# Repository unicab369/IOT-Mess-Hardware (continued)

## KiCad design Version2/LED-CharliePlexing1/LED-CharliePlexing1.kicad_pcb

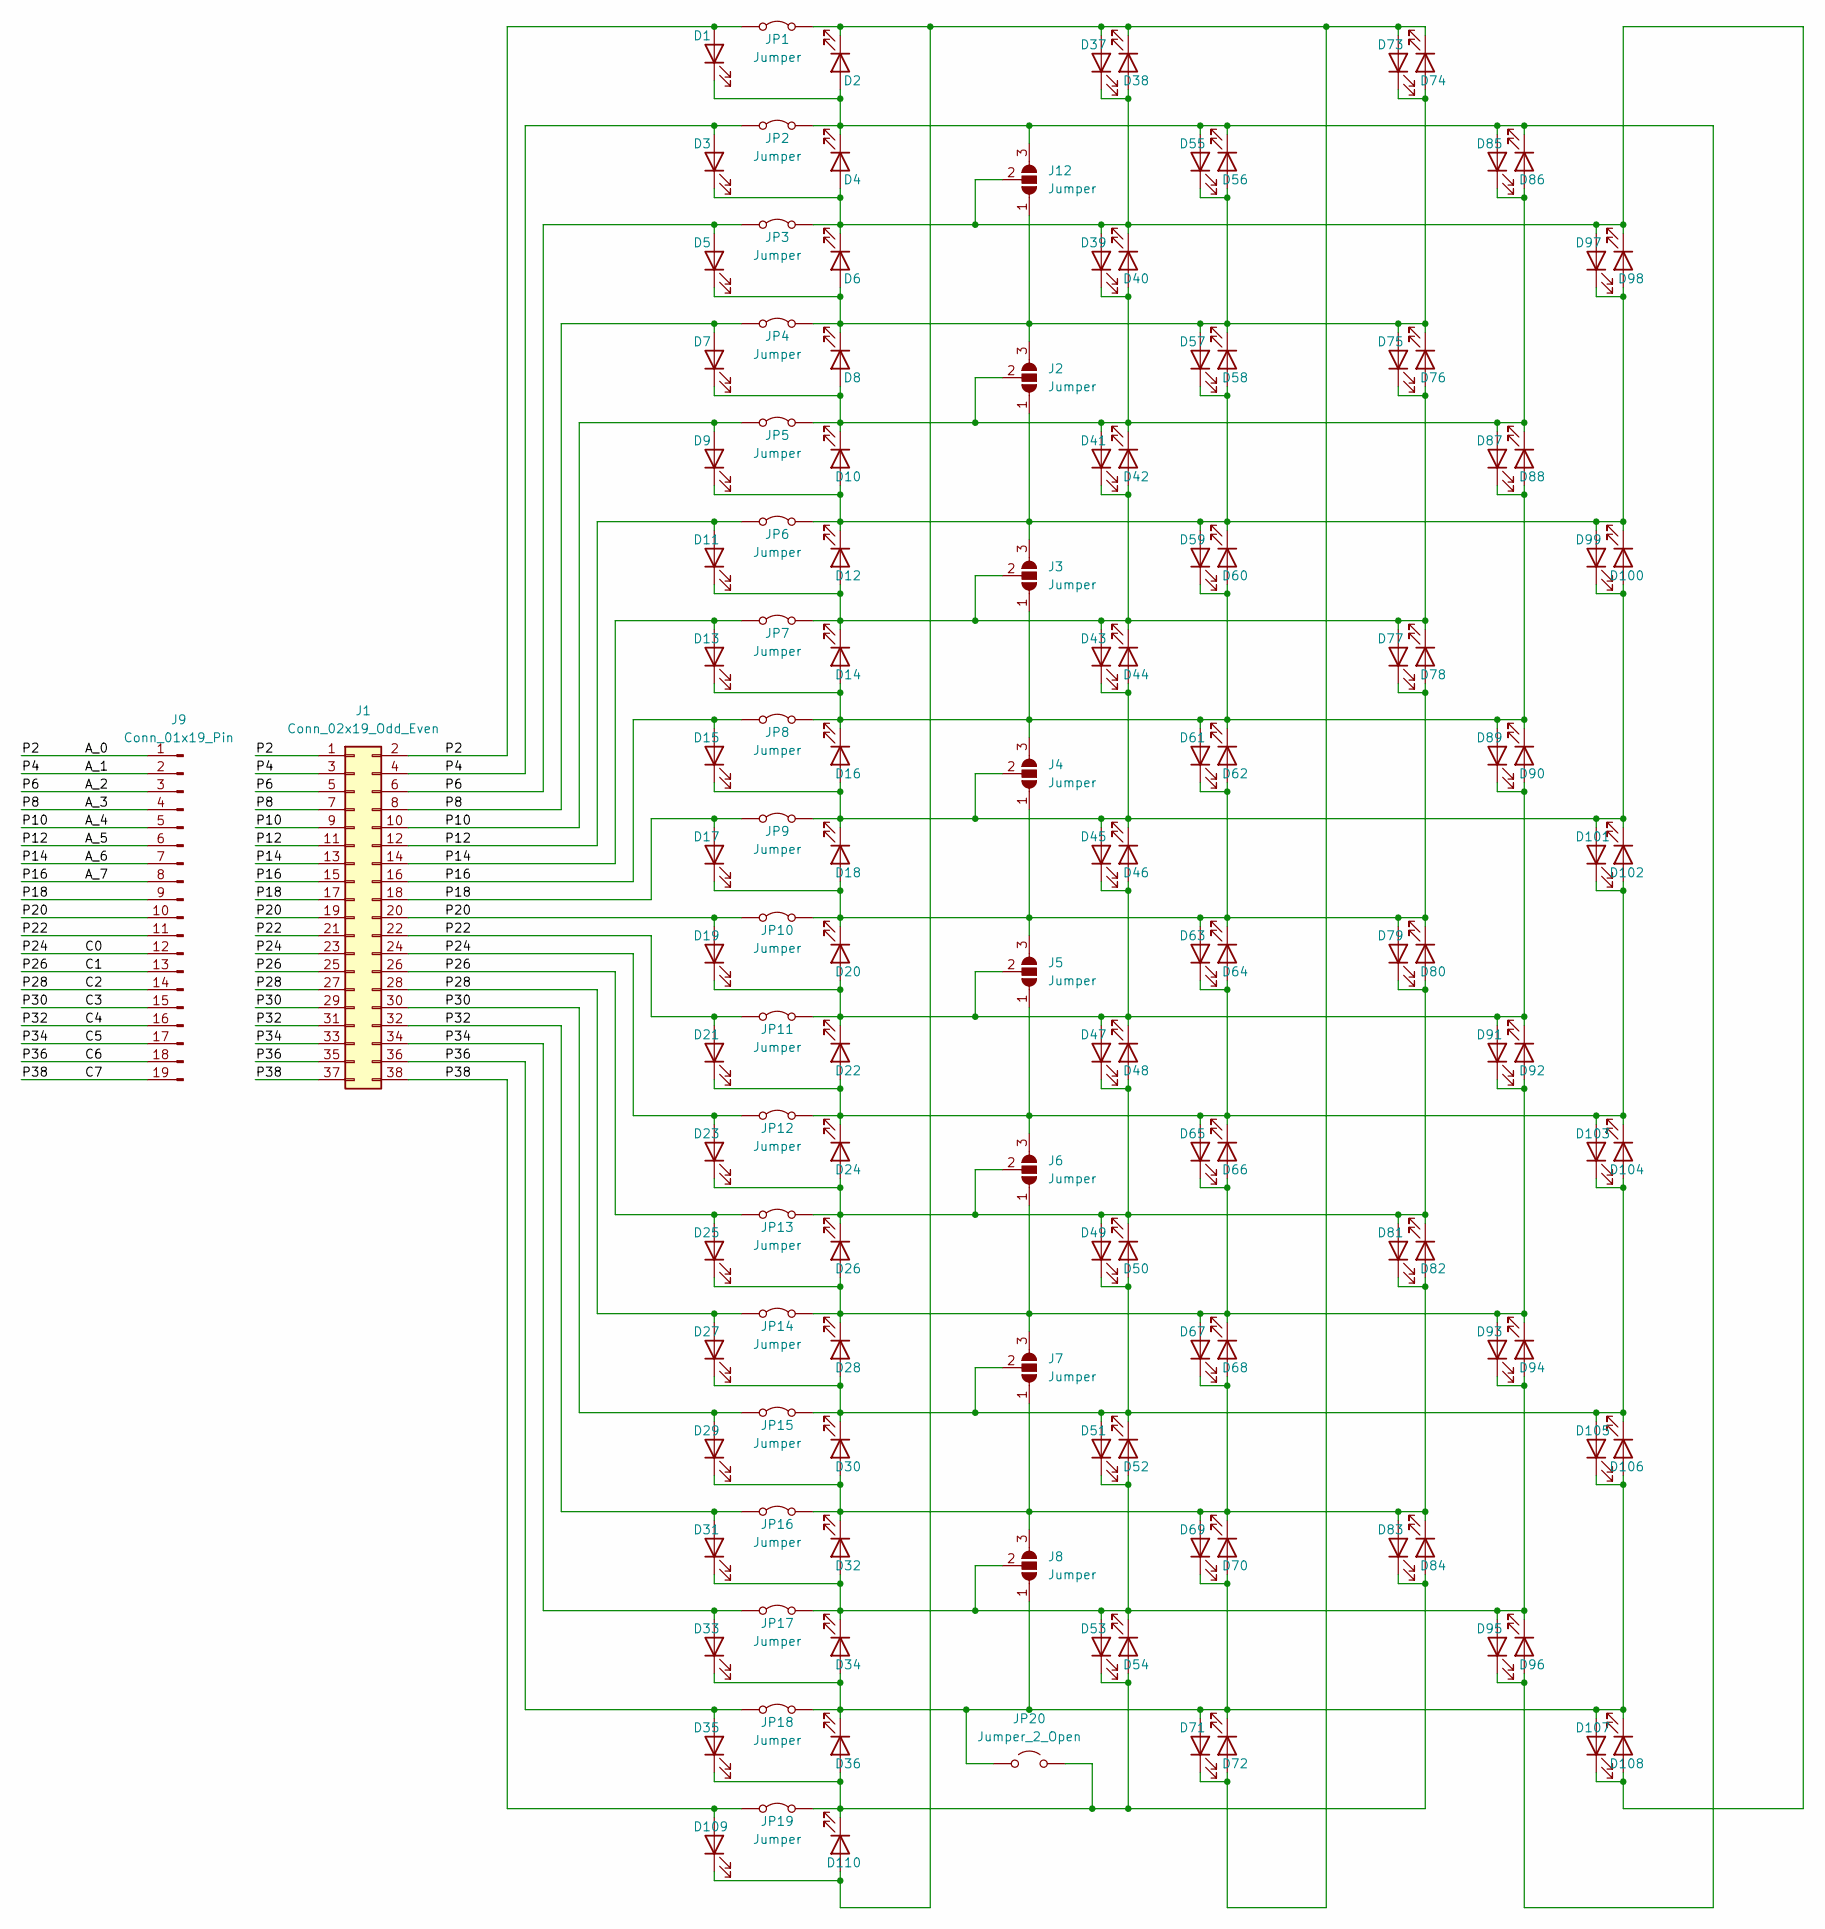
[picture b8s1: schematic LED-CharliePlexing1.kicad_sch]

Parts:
D1, D2, D3, D4, D5, D6, D7, D8, D9, D10, D11, D12, D13, D14, D15, D16, D17, D18, D19, D20, D21, D22, D23, D24, D25, D26, D27, D28, D29, D30, D31, D32, D33, D34, D35, D36, D37, D38, D39, D40, D41, D42, D43, D44, D45, D46, D47, D48, D49, D50, D51, D52, D53, D54, D55, D56, D57, D58, D59, D60, D61, D62, D63, D64, D65, D66, D67, D68, D69, D70, D71, D72, D73, D74, D75, D76, D77, D78, D79, D80, D81, D82, D83, D84, D85, D86, D87, D88, D89, D90, D91, D92, D93, D94, D95, D96, D97, D98, D99, D100, D101, D102, D103, D104, D105, D106, D107, D108, D109, D110: LED; LED_0603_1608Metric_Pad1.05x0.95mm_HandSolder
J1: Conn_02x19_Odd_Even; PinHeader_2x19_P2.54mm_Vertical
J2, J3, J4, J5, J6, J7, J8, J12: Jumper; Jumper-3_P1.3mm_Open_RoundedPad1.0x1.5mm
J9: Conn_01x19_Pin; PinHeader_1x19_P2.54mm_Vertical
JP1, JP2, JP3, JP4, JP5, JP6, JP7, JP8, JP9, JP10, JP11, JP12, JP13, JP14, JP15, JP16, JP17, JP18, JP19: Jumper; SolderJumper-2_P1.3mm_Bridged_RoundedPad1.0x1.5mm
JP20: Jumper_2_Open; SolderJumper-2_P1.3mm_Open_Pad1.0x1.5mm

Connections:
/A_0: D1.2 (A), J1.1, J1.2, J9.1, JP1.1 (A)
/A_1: D3.2 (A), J1.3, J1.4, J9.2, JP2.1 (A)
/A_2: D5.2 (A), J1.5, J1.6, J9.3, JP3.1 (A)
/A_3: D7.2 (A), J1.7, J1.8, J9.4, JP4.1 (A)
/A_4: D9.2 (A), J1.9, J1.10, J9.5, JP5.1 (A)
/A_5: D11.2 (A), J1.11, J1.12, J9.6, JP6.1 (A)
/A_6: D13.2 (A), J1.13, J1.14, J9.7, JP7.1 (A)
/A_7: D15.2 (A), J1.15, J1.16, J9.8, JP8.1 (A)
/C0: D23.2 (A), J1.23, J1.24, J9.12, JP12.1 (A)
/C1: D25.2 (A), J1.25, J1.26, J9.13, JP13.1 (A)
/C2: D27.2 (A), J1.27, J1.28, J9.14, JP14.1 (A)
/C3: D29.2 (A), J1.29, J1.30, J9.15, JP15.1 (A)
/C4: D31.2 (A), J1.31, J1.32, J9.16, JP16.1 (A)
/C5: D33.2 (A), J1.33, J1.34, J9.17, JP17.1 (A)
/C6: D35.2 (A), J1.35, J1.36, J9.18, JP18.1 (A)
/C7: D109.2 (A), J1.37, J1.38, J9.19, JP19.1 (A)
/P18: D17.2 (A), J1.17, J1.18, J9.9, JP9.1 (A)
/P20: D19.2 (A), J1.19, J1.20, J9.10, JP10.1 (A)
/P22: D21.2 (A), J1.21, J1.22, J9.11, JP11.1 (A)
unnamed: D1.1 (K), D2.2 (A), D4.1 (K), D55.2 (A), D56.1 (K), D85.2 (A), D86.1 (K), D95.1 (K), D96.2 (A), J12.3 (B), JP2.2 (B)
unnamed: D5.1 (K), D6.2 (A), D8.1 (K), D55.1 (K), D56.2 (A), D57.2 (A), D58.1 (K), D73.1 (K), D74.2 (A), D75.2 (A), D76.1 (K), J2.3 (B), J12.1 (A), JP4.2 (B)
unnamed: D9.1 (K), D10.2 (A), D12.1 (K), D57.1 (K), D58.2 (A), D59.2 (A), D60.1 (K), D97.1 (K), D98.2 (A), D99.2 (A), D100.1 (K), J2.1 (A), J3.3 (B), JP6.2 (B)
unnamed: D7.1 (K), D8.2 (A), D10.1 (K), D39.1 (K), D40.2 (A), D41.2 (A), D42.1 (K), D85.1 (K), D86.2 (A), D87.2 (A), D88.1 (K), J2.2 (C), JP5.2 (B)
unnamed: D11.1 (K), D12.2 (A), D14.1 (K), D41.1 (K), D42.2 (A), D43.2 (A), D44.1 (K), D75.1 (K), D76.2 (A), D77.2 (A), D78.1 (K), J3.2 (C), JP7.2 (B)
unnamed: D13.1 (K), D14.2 (A), D16.1 (K), D59.1 (K), D60.2 (A), D61.2 (A), D62.1 (K), D87.1 (K), D88.2 (A), D89.2 (A), D90.1 (K), J3.1 (A), J4.3 (B), JP8.2 (B)
unnamed: D17.1 (K), D18.2 (A), D20.1 (K), D61.1 (K), D62.2 (A), D63.2 (A), D64.1 (K), D77.1 (K), D78.2 (A), D79.2 (A), D80.1 (K), J4.1 (A), J5.3 (B), JP10.2 (B)
unnamed: D19.1 (K), D20.2 (A), D22.1 (K), D45.1 (K), D46.2 (A), D47.2 (A), D48.1 (K), D89.1 (K), D90.2 (A), D91.2 (A), D92.1 (K), J5.2 (C), JP11.2 (B)
unnamed: D23.1 (K), D24.2 (A), D26.1 (K), D47.1 (K), D48.2 (A), D49.2 (A), D50.1 (K), D79.1 (K), D80.2 (A), D81.2 (A), D82.1 (K), J6.2 (C), JP13.2 (B)
unnamed: D25.1 (K), D26.2 (A), D28.1 (K), D65.1 (K), D66.2 (A), D67.2 (A), D68.1 (K), D91.1 (K), D92.2 (A), D93.2 (A), D94.1 (K), J6.1 (A), J7.3 (B), JP14.2 (B)
unnamed: D29.1 (K), D30.2 (A), D32.1 (K), D67.1 (K), D68.2 (A), D69.2 (A), D70.1 (K), D81.1 (K), D82.2 (A), D83.2 (A), D84.1 (K), J7.1 (A), J8.3 (B), JP16.2 (B)
unnamed: D31.1 (K), D32.2 (A), D34.1 (K), D51.1 (K), D52.2 (A), D53.2 (A), D54.1 (K), D93.1 (K), D94.2 (A), D95.2 (A), D96.1 (K), J8.2 (C), JP17.2 (B)
unnamed: D15.1 (K), D16.2 (A), D18.1 (K), D43.1 (K), D44.2 (A), D45.2 (A), D46.1 (K), D99.1 (K), D100.2 (A), D101.2 (A), D102.1 (K), J4.2 (C), JP9.2 (B)
unnamed: D21.1 (K), D22.2 (A), D24.1 (K), D63.1 (K), D64.2 (A), D65.2 (A), D66.1 (K), D101.1 (K), D102.2 (A), D103.2 (A), D104.1 (K), J5.1 (A), J6.3 (B), JP12.2 (B)
unnamed: D27.1 (K), D28.2 (A), D30.1 (K), D49.1 (K), D50.2 (A), D51.2 (A), D52.1 (K), D103.1 (K), D104.2 (A), D105.2 (A), D106.1 (K), J7.2 (C), JP15.2 (B)
unnamed: D33.1 (K), D34.2 (A), D36.1 (K), D69.1 (K), D70.2 (A), D71.2 (A), D72.1 (K), D105.1 (K), D106.2 (A), D107.2 (A), D108.1 (K), J8.1 (A), JP18.2 (B), JP20.1 (A)
unnamed: D3.1 (K), D4.2 (A), D6.1 (K), D37.1 (K), D38.2 (A), D39.2 (A), D40.1 (K), D97.2 (A), D98.1 (K), D107.1 (K), D108.2 (A), J12.2 (C), JP3.2 (B)
unnamed: D2.1 (K), D37.2 (A), D38.1 (K), D71.1 (K), D72.2 (A), D73.2 (A), D74.1 (K), D109.1 (K), D110.2 (A), JP1.2 (B)
unnamed: D35.1 (K), D36.2 (A), D53.1 (K), D54.2 (A), D83.1 (K), D84.2 (A), D110.1 (K), JP19.2 (B), JP20.2 (B)

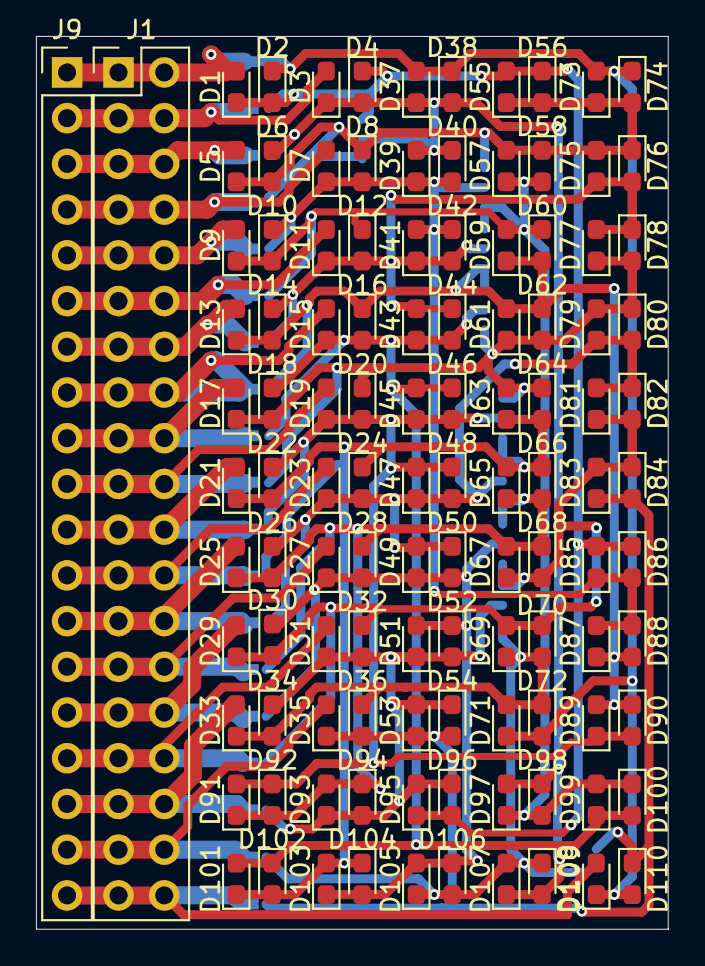
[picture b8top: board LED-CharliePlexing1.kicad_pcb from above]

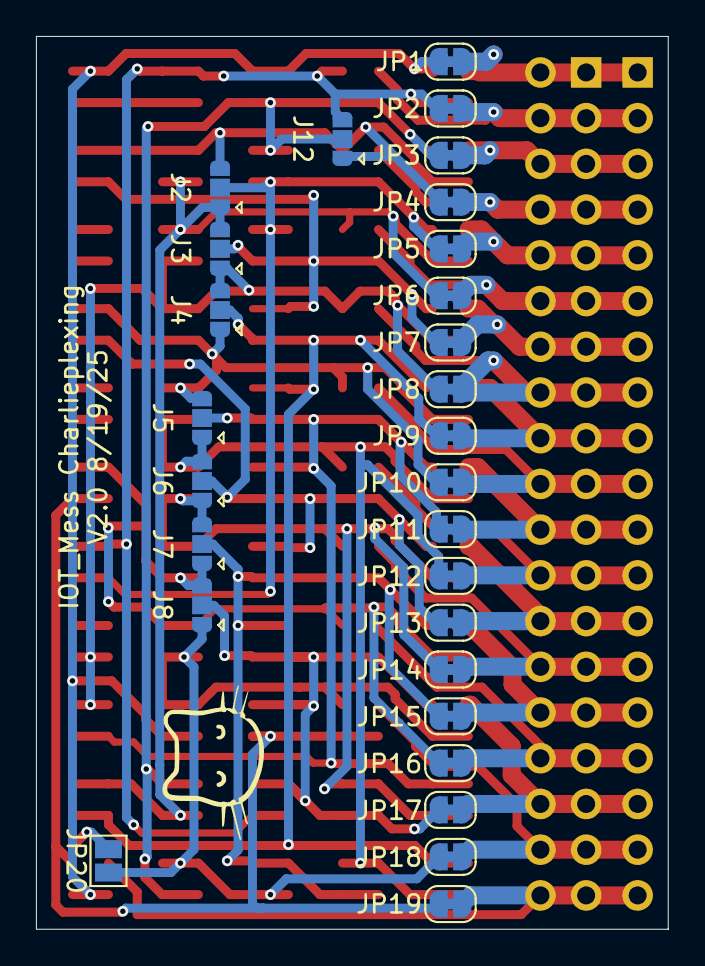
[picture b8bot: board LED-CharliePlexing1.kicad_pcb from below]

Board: 2 copper layers, 35.1 x 49.6 mm, 140 parts (28 on the bottom side), 38 nets.

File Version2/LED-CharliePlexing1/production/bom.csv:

Designator,Footprint,Quantity,Value,LCSC Part #
"D1, D10, D100, D101, D102, D103, D104, D105, D106, D107, D108, D109, D11, D110, D12, D13, D14, D15, D16, D17, D18, D19, D2, D20, D21, D22, D23, D24, D25, D26, D27, D28, D29, D3, D30, D31, D32, D33, D34, D35, D36, D37, D38, D39, D4, D40, D41, D42, D43, D44, D45, D46, D47, D48, D49, D5, D50, D51, D52, D53, D54, D55, D56, D57, D58, D59, D6, D60, D61, D62, D63, D64, D65, D66, D67, D68, D69, D7, D70, D71, D72, D73, D74, D75, D76, D77, D78, D79, D8, D80, D81, D82, D83, D84, D85, D86, D87, D88, D89, D9, D90, D91, D92, D93, D94, D95, D96, D97, D98, D99",0603,110,LED,
J1,PinHeader_2x19_P2.54mm_Vertical,1,Conn_02x19_Odd_Even,
J9,PinHeader_1x19_P2.54mm_Vertical,1,Conn_01x19_Pin,
"JP1, JP10, JP11, JP12, JP13, JP14, JP15, JP16, JP17, JP18, JP19, JP2, JP3, JP4, JP5, JP6, JP7, JP8, JP9",SolderJumper-2_P1.3mm_Bridged_RoundedPad1.0x1.5mm,19,Jumper,
JP20,SolderJumper-2_P1.3mm_Open_Pad1.0x1.5mm,1,Jumper_2_Open,

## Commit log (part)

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2025-05-11 Initial commit.
2025-06-22 updates.
2025-06-28 did some works.
2025-08-06 added versions.
2025-08-08 added jumper boards.
2025-08-16 updated.
2025-08-20 update.
2025-08-26 update stuff.
2025-08-26 hardware updates.
2025-10-17 cleanup.
2025-12-17 added New Power circuit.
2025-12-18 update schematic.
